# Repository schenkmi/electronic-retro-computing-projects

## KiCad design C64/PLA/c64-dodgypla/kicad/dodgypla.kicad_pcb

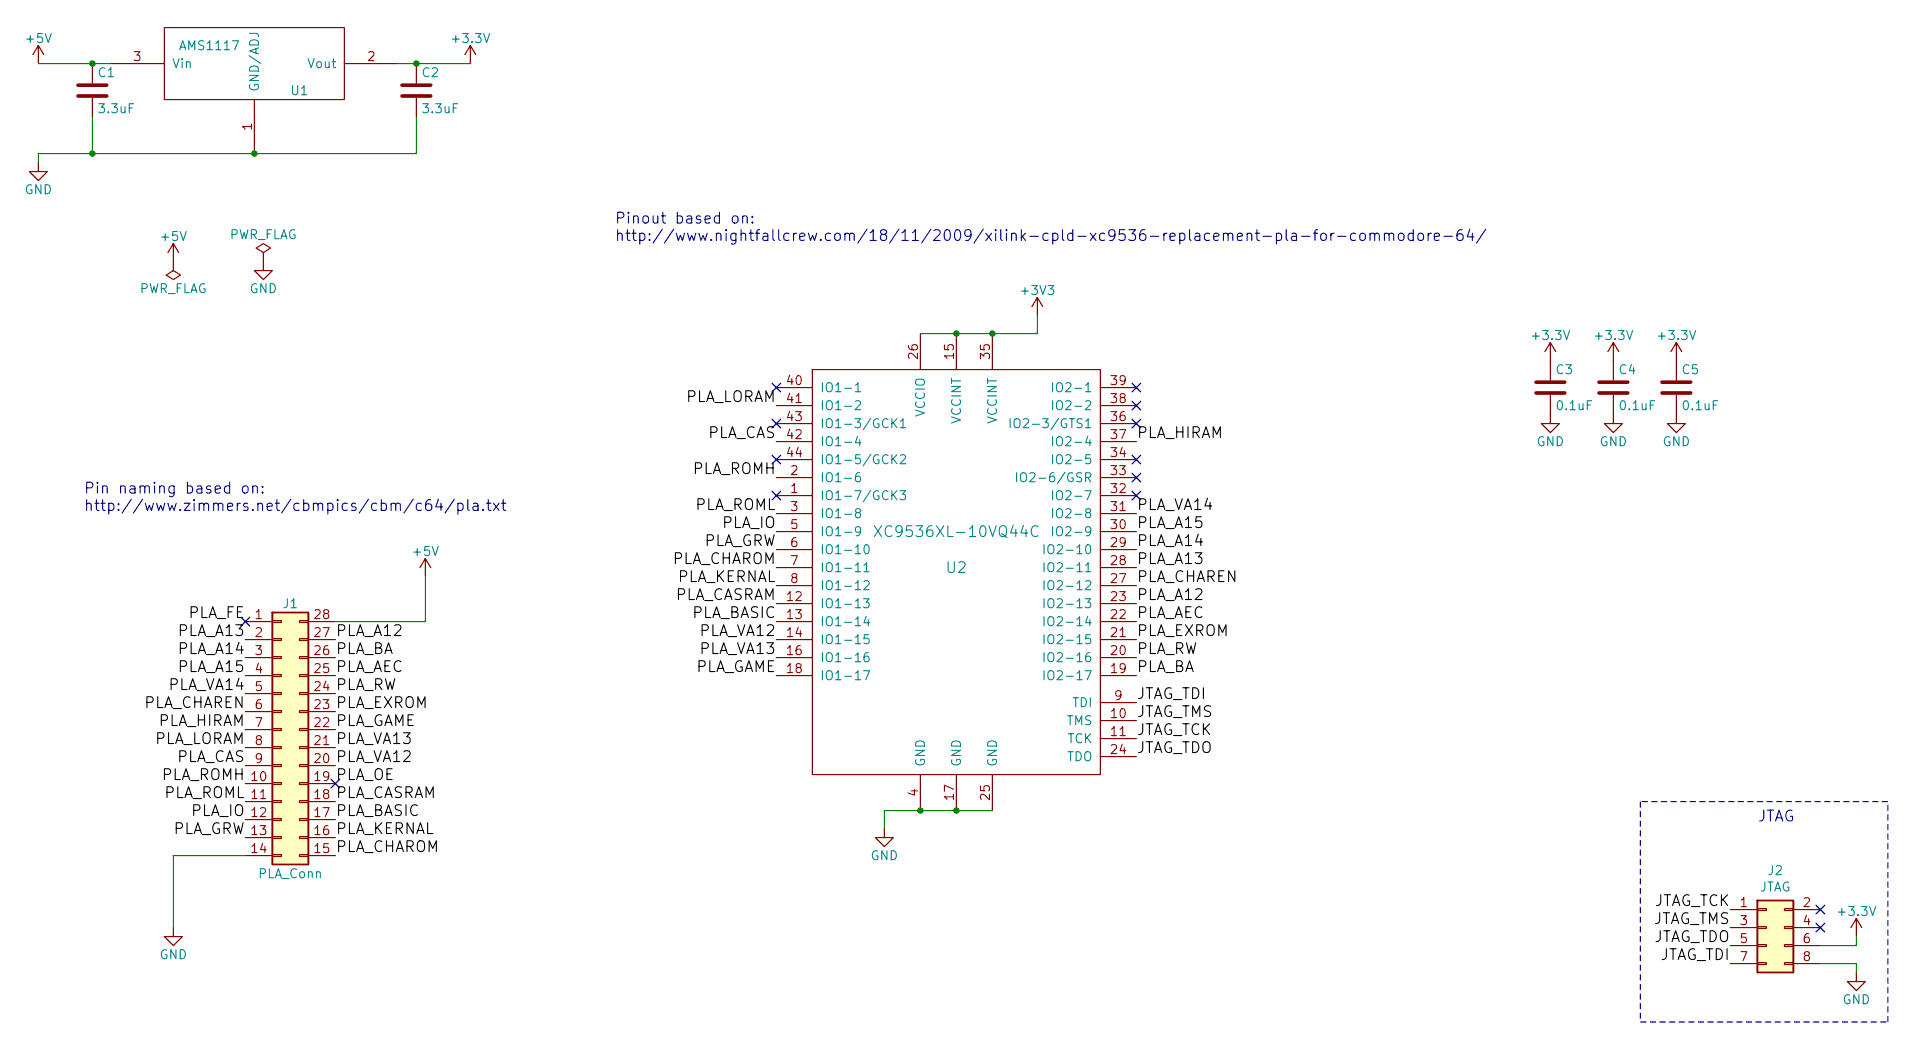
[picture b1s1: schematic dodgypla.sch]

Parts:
C1, C2: 3.3uF; C_0805
C3, C4, C5: 0.1uF; C_0805
J1: PLA_Conn; DIP-28_W15.24mm_Socket
J2: JTAG; Pin_Header_Straight_2x04_Pitch2.54mm
U1: AMS1117; SOT-223-3_TabPin2
U2: XC9536XL-10VQ44C; LQFP-44_10x10mm_P0.8mm

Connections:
+5V: C1.1, J1.28, U1.3 (Vin)
/JTAG_TCK: J2.1, U2.11 (TCK)
/JTAG_TDI: J2.7, U2.9 (TDI)
/JTAG_TDO: J2.5, U2.24 (TDO)
/JTAG_TMS: J2.3, U2.10 (TMS)
/PLA_A12: J1.27, U2.23 (IO2-13)
/PLA_A13: J1.2, U2.28 (IO2-11)
/PLA_A14: J1.3, U2.29 (IO2-10)
/PLA_A15: J1.4, U2.30 (IO2-9)
/PLA_AEC: J1.25, U2.22 (IO2-14)
/PLA_BA: J1.26, U2.19 (IO2-17)
/PLA_BASIC: J1.17, U2.13 (IO1-14)
/PLA_CAS: J1.9, U2.42 (IO1-4)
/PLA_CASRAM: J1.18, U2.12 (IO1-13)
/PLA_CHAREN: J1.6, U2.27 (IO2-12)
/PLA_CHAROM: J1.15, U2.7 (IO1-11)
/PLA_EXROM: J1.23, U2.21 (IO2-15)
/PLA_FE: J1.1
/PLA_GAME: J1.22, U2.18 (IO1-17)
/PLA_GRW: J1.13, U2.6 (IO1-10)
/PLA_HIRAM: J1.7, U2.37 (IO2-4)
/PLA_IO: J1.12, U2.5 (IO1-9)
/PLA_KERNAL: J1.16, U2.8 (IO1-12)
/PLA_LORAM: J1.8, U2.41 (IO1-2)
/PLA_OE: J1.19
/PLA_ROMH: J1.10, U2.2 (IO1-6)
/PLA_ROML: J1.11, U2.3 (IO1-8)
/PLA_RW: J1.24, U2.20 (IO2-16)
/PLA_VA12: J1.20, U2.14 (IO1-15)
/PLA_VA13: J1.21, U2.16 (IO1-16)
/PLA_VA14: J1.5, U2.31 (IO2-8)
GND: C1.2, C2.2, C3.2, C4.2, C5.2, J1.14, J2.8, U1.1 (GND/ADJ), U2.4 (GND), U2.17 (GND), U2.25 (GND)

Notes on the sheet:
Pin naming based on: http://www.zimmers.net/cbmpics/cbm/c64/pla.txt
Pinout based on: http://www.nightfallcrew.com/18/11/2009/xilink-cpld-xc9536-replacement-pla-for-commodore-64/
JTAG

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
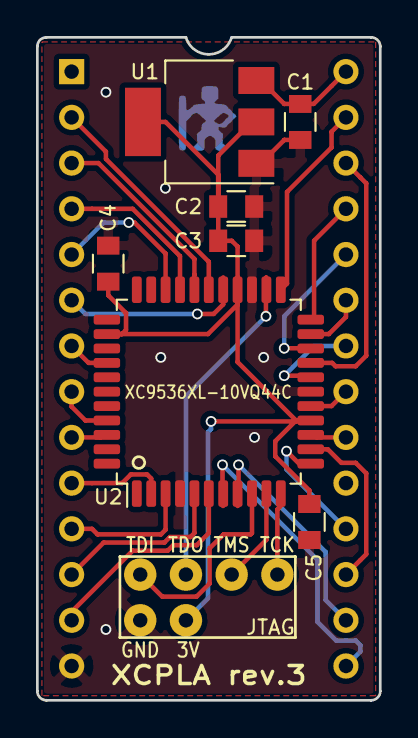
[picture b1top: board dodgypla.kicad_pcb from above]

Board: 2 copper layers, 19.0 x 36.8 mm, 9 parts (0 on the bottom side), 31 nets.

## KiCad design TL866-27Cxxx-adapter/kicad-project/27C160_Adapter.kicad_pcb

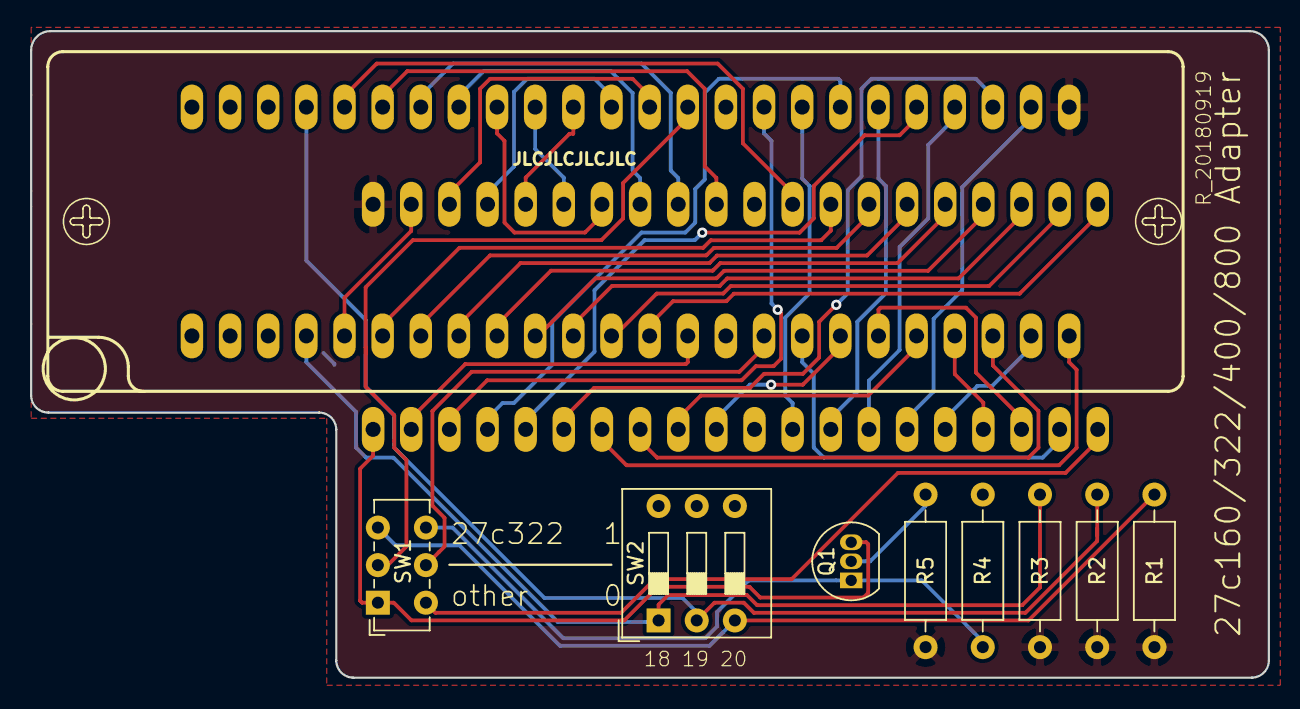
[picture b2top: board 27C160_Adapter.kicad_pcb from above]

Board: 2 copper layers, 82.4 x 43.1 mm, 11 parts (0 on the bottom side), 46 nets.

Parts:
Q1: BC327; TO-92_Inline
R1, R2, R3, R4, R5: 10k; R_Axial_DIN0207_L6.3mm_D2.5mm_P10.16mm_Horizontal
REF01: OSHW-Logo2_9.8x8mm_SilkScreen
SW1: MS22D16; SW_E-Switch_EG1271_DPDT
SW2: SW_DIP_x03; SW_DIP_SPSTx03_Slide_9.78x9.8mm_W7.62mm_P2.54mm
U1: 27C4002
ZX1: 3M_248-3345

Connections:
/A0: U1.21, ZX1.13
/A1: U1.22, ZX1.12
/A2: U1.23, ZX1.11
/A3: U1.24, ZX1.10
/A4: U1.25, ZX1.9
/A5: U1.26, ZX1.8
/A6: U1.27, ZX1.7
/A7: U1.28, ZX1.6
/A8: U1.29, ZX1.44
/A9: U1.31, ZX1.43
/A10: U1.32, ZX1.42
/A11: U1.33, ZX1.41
/A12: U1.34, ZX1.40
/A13: U1.35, ZX1.39
/A14: U1.36, ZX1.38
/A15: U1.37, ZX1.37
/A16: U1.38, ZX1.36
/A17: U1.39, ZX1.5
/A18: R3.1, SW2.1, ZX1.4
/A19: R2.1, SW2.2, ZX1.45
/A20: R1.1, SW1.3, SW2.3
/D0: U1.19, ZX1.17
/D1: U1.18, ZX1.19
/D2: U1.17, ZX1.21
/D3: U1.16, ZX1.23
/D4: U1.15, ZX1.26
/D5: U1.14, ZX1.28
/D6: U1.13, ZX1.30
/D7: U1.12, ZX1.32
/D8: U1.10, ZX1.18
/D9: U1.9, ZX1.20
/D10: U1.8, ZX1.22
/D11: U1.7, ZX1.24
/D12: U1.6, ZX1.27
/D13: U1.5, ZX1.29
/D14: U1.4, ZX1.31
/D15: U1.3, ZX1.33
/E: U1.2, ZX1.14
/N$1: Q1.2, R5.2
/N$2: SW1.2, ZX1.35
/N$4: Q1.1, R4.1, SW1.6
/N$5: SW1.4, U1.20
/N$6: SW1.5, ZX1.16
/VPP: Q1.3, SW1.1, U1.1
GND: R4.2, SW2.4, SW2.5, SW2.6, U1.11, U1.30, ZX1.15, ZX1.34
VCC: R1.2, R2.2, R3.2, R5.1, U1.40, ZX1.25

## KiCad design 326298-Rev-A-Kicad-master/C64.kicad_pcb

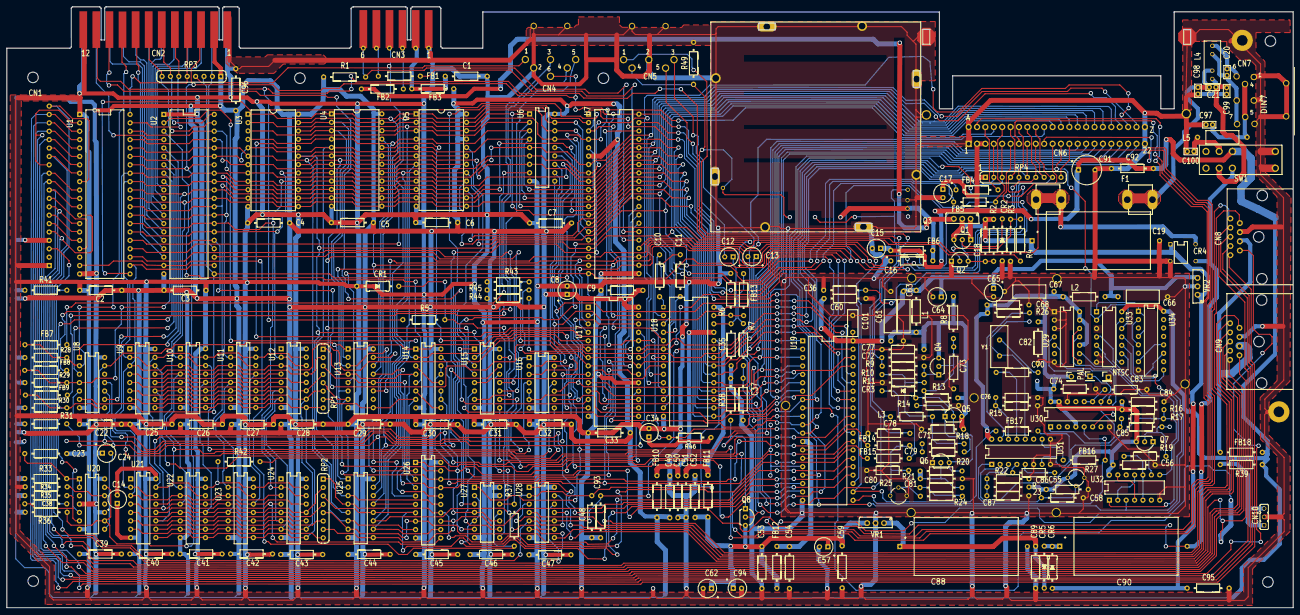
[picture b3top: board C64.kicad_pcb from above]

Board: 2 copper layers, 389.2 x 181.8 mm, 237 parts (0 on the bottom side), 234 nets.

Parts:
C1, C2, C3, C16, C18, C22, C30, C31, C32, C35, C39, C45, C46, C47, C55, C56, C58, C68, C71, C74, C76, C77, C82, C84, C87, C89, C95, C96: 0.1 uF; 12_03_07
C4, C5, C6, C7, C9, C29, C33, C44, C51, C60, C85: 0.47 uF; 12_03_07
C8, C12, C13, C14, C15, C17, C24, C34, C57, C62, C64, C65, C94: 10 uF 25V; CAPACITOR_ELECTROLYTIC_2.5_6
C10, C11: 2200 pF Polyester; polyester12_03_07
C19: 2200 uF 16V; E37-31.5-17.5-E
C20, C21, C97, C98, C99, C100: 0.22 uF 100V; 0203
C23: 360 pF; 12_03_07
C25, C26, C27, C28, C40, C41, C42, C43, C50, C53, C59, C92: 0.22 uF; 12_03_07
C36: 20 pF 50V; 12_03_07
C37, C48, C93: 1000 pF; 12_03_07
C38, C80: 51 pF; 12_03_07
C49, C52: 470 pF 50V; 12_03_07
C54: 470 pF; 12_03_07
C61, C63, C66, C67: 0.47 uF 50V 20%; 15_4_10
C70: 10 pF 5%; 12_03_07
C72, C78: 220 pF 50V; 12_03_07
C73: 150 pF 50V; 12_03_07
C79: 510 pF; 12_03_07
C81: 20 pF; 12_03_07
C83: 33 pF; 12_03_07
C86: 39 pF 50V 5%; 12_03_07
C88, C90: 470 uF 50V; E37-31.5-17.5-E
C91: 100 uF 16V; C_E_5-9
C101: 0.1 uF; c101
CN1: KEYBOARD; 20way
CN2: USERPORT
CN3: CASSETTEPORT
CN4: DIN6
CN5: DIN5
CN6: EXPANSIONPORT
CN7: DIN7
CN8, CN9: CONTROL_PORT
CN10: JP2E; 3way
CR1: 1N4371 2.7 V; D-12_3_7
CR2: 7.5 V; D-12_3_7
CR3: 1N914; D-12_3_7
CR4: BRIDGE_RECTIFIER
CR5, CR6: 1N4001; D-12_3_7
F1: 1A; SH32
FB1, FB2, FB3, FB4, FB5, FB6, FB7, FB8, FB9, FB10, FB11, FB12, FB13, FB14, FB15, FB16, FB17, FB18: FERRITE_BEAD
J1, J2, J3: Conn_01x01; Socket_Strip_Straight_1x01_Pitch2.54mm
L1, L2: 2.2 uH; 12_03_07
L3: 3 uH; 12_03_07
L4: LINEFILTER
L5: 1.2 uH; P15
Q1: 2N4401; TO92
Q2: 2N3904; TO92
Q3: TIP29B
Q4, Q5, Q6, Q7, Q8: PN2222; TO92
R1, R24, R43, R44, R45: 3.3 K; 12_03_07
R2, R5, R15, R22: 1.5 K; 12_03_07
R3, R7: 10 K; 12_03_07
R4, R6, R13, R16, R23, R28, R29, R30, R31, R36, R38: 1 K; 12_03_07
R8, R39: 390; 12_03_07
R9, R26: 75; 12_03_07
R10, R11: 120; 12_03_07
R14: 100; 12_03_07
R17: 1.2 K; 12_03_07
R18: 230; 12_03_07
R19: 15 K; 12_03_07
R20, R37: 6.8 K; 12_03_07
R21: 4.7 K; 12_03_07
R25: 1 K Trim Pot; POT_METER
R27: 2 K Trim Pot; POT_METER
R33, R34: 47 K; 12_03_07
R35: 470 K; 12_03_07
R41: 1 M; 12_03_07
R42: 0; 12_03_07
R46: 2.1 K; 12_03_07
R49: 470; 12_03_07
RF1: RF-MODULATOR
RP1, RP2: 33; RESISTOR_PACK_4
RP3: 3.3 K; RESISTOR_PACK_4
RP4: 3.3 K; RESISTOR_PACK_9
SW1: DPDT_SWITCH
U1, U2: 6526
U3, U4: 2364
U5: 2332
U6: 2114
U7: 6510
U8: SN7406NN
U9, U10, U11, U12, U21, U22, U23, U24: 4164
U13, U25: SN74257N
U14: SN74258N
U15: SN74139N
U16, U28: 4066
U17: C64PLA
U18: 6581
U19: 6569
U20: 556DIGITAL
U26: SN74373N; 74373N
U27: SN7408N
U29: SN7474N
U30: SN74193N
U31: SN74629
U32: MC4044
U33: 74LS02; 7402
U34: 74LS175; SN74629
VR1: 7812; VR
VR2: 7805; VR
Y1: 17.73 MHz; HC49TL-H

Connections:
/+5Vc: C55.1, C56.1, C67.1, C68.1, C74.1, C82.1, C84.1, J1.1, L2.2, Q7.3, R16.1, R23.1, R26.1, R27.E, U29.10, U29.13, U29.14, U30.4, U30.15, U30.16, U31.16, U32.14
/+5Vcan: C60.1, C63.1, C64.+, C65.+, C66.1, C101.1, L1.1, L2.1, U19.40, VR2.3
/+5Vvid: C61.1, C71.1, C77.1, L1.2, Q4.3, Q5.3, R8.1, R13.1
/+9V: C18.1, C19.+, C95.1, CR4.1, CR6.1, Q1.3, Q3.2, R2.1, VR2.1
/+12V: C52.1, C53.1, C57.+, C59.1, C62.+, C94.+, FB11.1, FB12.1, Q8.3, VR1.3
/A0: CN6.Y, U1.38, U2.38, U3.8, U4.8, U5.8, U6.5, U7.7, U18.9, U25.13, U26.6
/A1: CN6.X, U1.37, U2.37, U3.7, U4.7, U5.7, U6.6, U7.8, U18.10, U25.10, U26.12
/A2: CN6.W, U1.36, U2.36, U3.6, U4.6, U5.6, U6.7, U7.9, U18.11, U25.6, U26.9
/A3: CN6.V, U1.35, U2.35, U3.5, U4.5, U5.5, U6.4, U7.10, U18.12, U25.3, U26.15
/A4: CN6.U, U3.4, U4.4, U5.4, U6.3, U7.11, U13.13, U18.13, U26.16
/A5: CN6.T, U3.3, U4.3, U5.3, U6.2, U7.12, U13.6, U26.19
/A6: CN6.S, U3.2, U4.2, U5.2, U6.1, U7.13, U13.3, U26.5
/A7: CN6.R, U3.1, U4.1, U5.1, U6.17, U7.14, U26.2
/A8: CN6.P, U3.23, U4.23, U5.23, U6.16, U7.15, U15.14, U19.32, U25.14
/A9: CN6.N, U3.22, U4.22, U5.22, U6.15, U7.16, U15.13, U19.33, U25.11
/A10: CN6.M, U3.19, U4.19, U5.19, U7.17, U15.2, U19.34, U25.5
/A11: CN6.L, U3.18, U4.18, U5.18, U7.18, U15.3, U19.23, U25.2
/A12: CN6.K, RP4.9, U3.21, U4.21, U7.19, U13.14, U17.27
/A13: CN6.J, RP4.7, U7.20, U13.5, U17.2
/A14: CN6.H, RP4.5, U7.22, U13.2, U17.3
/A15: CN6.F, RP4.4, U7.23, U13.11, U17.4
/D0: CN6.21, U1.33, U2.33, U3.9, U4.9, U5.9, U7.37, U16.11, U18.15, U19.7, U21.2, U21.14
/D1: CN6.20, U1.32, U2.32, U3.10, U4.10, U5.10, U7.36, U9.2, U9.14, U16.8, U18.16, U19.6
/D2: CN6.19, U1.31, U2.31, U3.11, U4.11, U5.11, U7.35, U16.4, U18.17, U19.5, U22.2, U22.14
/D3: CN6.18, U1.30, U2.30, U3.13, U4.13, U5.13, U7.34, U10.2, U10.14, U16.1, U18.18, U19.4
/D4: CN6.17, U1.29, U2.29, U3.14, U4.14, U5.14, U7.33, U18.19, U19.3, U23.2, U23.14
/D5: CN6.16, U1.28, U2.28, U3.15, U4.15, U5.15, U7.32, U11.2, U11.14, U18.20, U19.2
/D6: CN6.15, U1.27, U2.27, U3.16, U4.16, U5.16, U7.31, U18.21, U19.1, U24.2, U24.14
/D7: CN6.14, U1.26, U2.26, U3.17, U4.17, U5.17, U7.30, U12.2, U12.14, U18.22, U19.39
/GND: C1.2, C2.2, C3.2, C4.2, C5.2, C6.2, C7.2, C8.-, C9.2, C14.-, C15.-, C16.2, C17.-, C19.-, C22.2, C23.2, C25.2, C26.2, C27.2, C28.2, C29.2, C30.2, C31.2, C32.2, C33.2, C34.-, C35.2, C36.2, C37.2, C39.2, C40.2, C41.2, C42.2, C43.2, C44.2, C45.2, C46.2, C47.2, C48.1, C49.2, C50.2, C51.2, C52.2, C53.2, C54.2, C55.2, C56.2, C57.-, C58.2, C59.2, C60.2, C61.2, C62.-, C63.2, C64.-, C65.-, C66.2, C67.2, C68.2, C71.2, C72.2, C73.2, C74.2, C76.2, C77.2, C78.2, C80.2, C82.2, C83.2, C84.2, C87.2, C88.-, C89.2, C91.-, C92.2, C93.1, C94.-, C95.2, C96.2, C97.2, C98.2, C99.2, C100.2, C101.2, CN1.1, CN2.1, CN2.12, CN2.A, CN2.N, CN3.1, CN3.A, CN4.2, CN4.PE, CN4.PE@, CN5.2, CN5.PE, CN5.PE@, CN6.1, CN6.22, CN6.A, CN6.P$1, CN6.P$2, CN6.P$3, CN6.P$4, CN6.Z, CN7.1, CN7.2, CN7.3, CN7.PE, CN7.PE@, CN8.8, CN9.8, CN10.2, CR1.1, CR2.1, CR4.2, J2.1, Q2.1, Q6.1, R3.2, R6.2, R11.1, R14.2, R15.2, R21.2, R22.2, R25.E, R27.A, R34.1, R38.2, R49.2, RF1.CASE, RF1.P$1, RF1.P$2, RF1.P$3, RF1.P$4, RF1.P$5, RF1.P$6, RF1.P$7, RF1.P$8, SW1.7, SW1.8, U1.1, U2.1, U3.12, U4.12, U5.12, U6.9, U7.21, U8.7, U9.16, U10.16, U11.16, U12.16, U13.8, U14.8, U15.8, U16.7, U17.14, U17.19, U18.14, U19.20, U20.7, U21.16, U22.16, U23.16, U24.16, U25.8, U26.10, U27.7, U28.7, U29.1, U29.2, U29.3, U29.7, U30.8, U30.14, U31.6, U31.8, U31.9, U32.7, U33.3, U33.6, U33.7, U34.8, VR1.2, VR2.2
/IRQ: CN6.4, RP4.2, U1.21, U7.3, U19.8
/MA0: RP2.4, U9.5, U10.5, U11.5, U12.5, U21.5, U22.5, U23.5, U24.5
/MA1: RP2.8, U9.7, U10.7, U11.7, U12.7, U21.7, U22.7, U23.7, U24.7
/MA2: RP2.6, U9.6, U10.6, U11.6, U12.6, U21.6, U22.6, U23.6, U24.6
/MA3: RP2.2, U9.12, U10.12, U11.12, U12.12, U21.12, U22.12, U23.12, U24.12
/MA4: RP1.4, U9.11, U10.11, U11.11, U12.11, U21.11, U22.11, U23.11, U24.11
/MA5: RP1.6, U9.10, U10.10, U11.10, U12.10, U21.10, U22.10, U23.10, U24.10
/MA6: RP1.2, U9.13, U10.13, U11.13, U12.13, U21.13, U22.13, U23.13, U24.13
/MA7: RP1.8, U9.9, U10.9, U11.9, U12.9, U21.9, U22.9, U23.9, U24.9
/N$1: C12.+, C35.1, U18.26
/N$2: FB13.1, R6.1, U18.27
/N$3: FB13.2, R7.1
/N$4: C37.1, Q8.2, R7.2
/N$5: C13.+, Q8.1, R38.1
/N$6: C10.2, U18.2
/N$7: C11.2, U18.4
/N$8: C10.1, U18.1
/N$9: C11.1, U18.3
/N$10: C13.-, CN5.3, RF1.AUDI
/N$11: C12.-, CN5.5
/N$12: C34.+, C50.1, FB10.1, R46.1, U18.25
/N$13: C16.1, FB6.2, RF1.+
/N$14: C51.1, FB11.2, U18.28
/N$15: C80.1, FB14.2, R25.A
/N$16: FB14.1, U19.14
/N$17: C97.1, CN7.4, CN7.5, L5.1
/N$18: C100.1, L5.2, SW1.2
/N$19: C20.2, CN7.6, L4.4
/N$20: C20.1, CN7.7, L4.2
/N$21: C21.1, C98.1, F1.1A, F1.1B, L4.3
/N$22: C21.2, C99.1, L4.1, SW1.5
/N$23: CN2.11, CR4.4, F1.2A, F1.2B, R5.1
/N$24: C90.-, CN2.10, CR4.3, SW1.6
/N$26: C90.+, CR5.1, CR6.2
/N$27: C88.+, C89.1, CR5.2, VR1.1
/N$28: R24.1, R25.S
/N$29: C81.2, R24.2
/N$30: C81.1, Q6.2, R20.1, R21.1
/N$31: Q5.2, Q6.3, R13.2, R20.2
/N$32: C79.2, Q5.1, R14.1
/N$33: L3.1, R10.2, R11.2, R18.1
/N$35: C54.1, FB12.2, U19.13
/N$36: C73.1, CR3.1, Q4.2, R8.2
/N$37: CR3.2, FB15.2
/N$38: Q4.1, R9.1, R10.1
/N$39: C72.1, CN5.1, R9.2
/N$41: C78.1, CN5.4, L3.2, R49.1, RF1.VIDE
/N$42: U14.10, U14.11, U19.31
/N$44: U14.13, U14.14, U19.30
/N$45: U14.3, U14.12
/N$46: U14.6, U14.9
/N$47: U6.14, U16.10, U19.38
/N$48: U6.13, U16.9, U19.37
/N$49: U6.12, U16.3, U19.36
/N$50: U6.11, U16.2, U19.35
/N$51: R42.2, U17.18
/N$52: U8.11, U14.15, U16.5, U16.6, U16.12, U16.13, U19.16, U26.1, U27.4, U27.10
/N$53: U8.13, U13.1, U14.1, U17.9, U19.19, U25.1
/N$54: R42.1, U9.15, U10.15, U11.15, U12.15, U21.15, U22.15, U23.15, U24.15
/N$55: U9.4, U10.4, U11.4, U12.4, U19.18, U21.4, U22.4, U23.4, U24.4, U26.11
/N$56: U6.8, U27.8
/N$59: C24.-, R34.2, U20.8, U20.12
/N$60: U8.5, U20.5
/N$61: C23.1, R33.2, U20.1, U20.2
/N$62: C38.2, R35.1, U20.6
/N$63: C38.1, CN1.3, R41.2
/N$64: R26.2, U31.15
/N$65: C58.1, R27.S, U31.1
/N$66: FB16.1, U31.10
/N$67: C70.2, U31.13
/N$68: U31.12, Y1.2
/N$69: C70.1, Y1.1
/N$70: FB16.2, U19.21, U30.5
/N$71: C83.1, U30.11, U30.12
/N$72: J3.1, U29.4, U30.1, U30.10
/N$73: U29.5, U30.9
/N$74: R16.2, R17.2, U31.2, U32.8
/N$75: U29.11, U30.6
/N$76: U29.8, U29.12
/N$77: U32.2, U32.11
/N$78: U32.4, U32.13
/N$79: C87.1, R22.1, R23.2, U31.3
/N$80: C86.1, U31.4
/N$81: C86.2, U31.5
/N$82: FB17.1, U31.7
/N$83: U29.9, U32.1
/N$84: CN3.5, CN3.E, FB1.1
/N$85: R19.2, U32.5, U32.10
/N$86: C85.1, R17.1
/N$87: C36.1, CN6.6, FB17.2, U19.22
/N$88: C85.2, Q7.2, R19.1
/N$89: R31.2, U8.10, U13.15, U17.25, U25.15
/N$90: Q7.1, U32.9
/N$91: CN1.19, CN8.2, U1.3
/N$92: CN1.18, CN8.3, U1.4
/N$93: CN1.17, CN8.4, U1.5
/N$94: CN1.16, CN8.6, U1.6
/N$95: CN1.15, U1.7
/N$96: CN1.14, U1.8, U28.6, U28.12
/N$97: CN1.20, U1.9, U28.5, U28.13
/N$98: CN1.13, CN8.1, U1.2
/N$99: CN1.12, CN9.1, U1.10
/N$100: CN1.11, CN9.2, U1.11
/N$101: CN1.10, CN9.3, U1.12
/N$102: CN1.9, U1.17
/N$103: CN1.8, CN9.6, U1.14, U19.9
/N$104: CN1.7, U1.15
/N$105: CN1.5, CN9.4, U1.13
/N$106: CN1.6, U1.16
/N$107: CN8.9, U28.1
/N$108: CN8.5, U28.4
/N$109: CN8.7, CN9.7, FB18.1
/N$110: CN9.9, U28.8
/N$111: CN9.5, U28.11
/N$112: C48.2, U18.24, U28.2, U28.9
/N$113: C93.2, U18.23, U28.3, U28.10
/N$114: CN4.3, FB7.1
/N$115: CN4.4, FB9.1
/N$116: CN4.5, FB8.1
/N$117: FB8.2, R29.2, U2.9, U8.4
/N$118: FB9.2, R30.2, U2.8, U8.8
/N$119: CN2.9, FB7.2, R28.2, U8.2
/N$120: CN2.8, U2.18
/N$121: CN2.L, U2.17
/N$122: CN2.K, U2.16
/N$123: CN2.J, U2.15
/N$124: CN2.H, U2.14
/N$125: CN2.F, U2.13
/N$126: CN2.E, U2.12
/N$127: CN2.D, U2.11
/N$128: CN2.C, U2.10
/N$129: CN2.B, RP3.2, U2.24
/N$130: U2.7, U8.3
/N$131: U2.6, U8.9
/N$132: U2.5, U8.1
/N$133: CN3.3, CN3.C, FB2.1
/N$134: CN2.4, RP3.5, U1.40
/N$135: U2.2, U14.2, U17.5
/N$136: U2.3, U14.5
/N$137: CN2.M, U2.4
/N$138: CN2.7, RP3.8, U2.39
/N$139: CN2.6, RP3.7, U2.40
/N$140: CN2.5, RP3.6, U1.39
/N$141: FB5.1, U7.39
/N$143: C76.1, R15.1, U31.14
/N$145: U3.20, U17.17
/N$146: CR1.2, R5.2, R37.2, U27.12
/N$147: R37.1, U1.19, U2.19, U27.11
/N$148: CN10.1, CN10.3, R39.2
/N$152: U4.20, U17.16
/N$153: CN6.C, FB4.1
/N$155: CN6.12, U17.26, U19.12, U27.1, U33.2, U33.12
/N$157: CN6.11, U17.11
/N$158: CN6.B, U17.10
/N$159: CN6.9, RP4.8, U17.23
/N$160: CN6.8, RP4.6, U17.22
/N$162: FB15.1, U19.15
/N$163: U15.4, U19.10
/N$164: R45.2, U7.29, U17.8
/N$165: R44.2, U7.28, U17.7
/N$166: R43.2, U7.27, U17.6
/N$167: U7.2, U27.3
/N$168: U7.5, U27.6
/N$169: CN6.13, RP4.10, U27.2, U27.5
/N$170: U5.20, U17.15
/N$171: CN3.4, CN3.D, CN4.1, RP3.4, U1.24
/N$172: CN3.6, CN3.F, R1.2, U7.25
/N$173: C1.1, CN3.2, CN3.B, FB3.1
/N$176: FB1.2, U7.26
/N$177: Q2.2, R3.1, R4.2
/N$178: Q1.1, Q3.1
/N$179: C18.2, CR2.2, Q1.2, Q2.3, R2.2
/N$180: FB2.2, Q3.3
/N$181: R4.1, U7.24
/N$182: U1.23, U15.12
/N$183: U2.23, U15.11
/N$184: U6.10, U17.13
/N$185: U15.1, U17.12
/N$186: U15.7, U15.15
/N$187: CN6.7, U15.10
/N$188: CN6.10, U15.9
/N$189: U15.5, U18.8
/N$190: U15.6, U27.9
/NA0: RP2.3, U19.24, U25.12, U26.7
/NA1: RP2.7, U19.25, U25.9, U26.13
/NA2: RP2.5, U19.26, U25.7, U26.8
/NA3: RP2.1, U19.27, U25.4, U26.14
/NA4: RP1.3, U13.12, U17.20, U19.28, U26.17
/NA5: RP1.5, U13.7, U17.21, U19.29, U26.18
/NA6: RP1.1, U13.4, U14.4, U26.4
/NA7: RP1.7, U13.9, U14.7, U26.3
/NMI: CN6.D, RP3.3, U2.21, U7.4, U8.6
/PHI0: U7.1, U19.17, U32.3, U33.5
/PHI2: CN6.E, FB5.2, U1.25, U2.25, U18.6
/RES: CN2.3, CN4.6, FB4.2, R36.2, U1.34, U2.34, U7.40, U18.5, U20.9, U20.13
/RW: CN6.5, R46.2, RP4.3, U1.22, U2.22, U7.38, U9.3, U10.3, U11.3, U12.3, U17.24, U18.7, U19.11, U21.3, U22.3, U23.3, U24.3
/VCC: C2.1, C3.1, C4.1, C5.1, C6.1, C7.1, C8.+, C9.1, C14.+, C15.+, C17.+, C22.1, C24.+, C25.1, C26.1, C27.1, C28.1, C29.1, C30.1, C31.1, C32.1, C33.1, C39.1, C40.1, C41.1, C42.1, C43.1, C44.1, C45.1, C46.1, C47.1, C49.1, C91.+, C92.1, C96.1, CN1.4, CN2.2, CN6.2, CN6.3, FB3.2, FB6.1, FB10.2, FB18.2, R1.1, R28.1, R29.1, R30.1, R31.1, R33.1, R35.2, R36.1, R39.1, R41.1, R43.1, R44.1, R45.1, RP3.1, RP4.1, SW1.3, U1.20, U2.20, U3.24, U4.24, U5.21, U5.24, U6.18, U7.6, U8.14, U9.8, U10.8, U11.8, U12.8, U13.16, U14.16, U15.16, U16.14, U17.28, U20.4, U20.10, U20.14, U21.8, U22.8, U23.8, U24.8, U25.16, U26.20, U27.13, U27.14, U28.14, U33.14, U34.16
unnamed: C79.1, R18.2
unnamed: U33.1, U34.1, U34.4
unnamed: U33.4, U33.9, U34.9
unnamed: U33.11, U34.11
unnamed: U33.8, U33.13
unnamed: U34.2, U34.5
unnamed: U34.7, U34.12

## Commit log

2023-07-29 Adding misc retro computing projects from the inetnert
2024-07-10 DIMM Modul
2024-07-10 Adding KiCad Retro
2024-07-17 Add EPROM EMU NG from
    https://github.com/Kris-Sekula/EPROM-EMU-NG
    https://mygeekyhobby.com/2020/07/05/eprom-emulator/
2024-07-20 https://github.com/MicroCoreLabs
    https://github.com/MicroCoreLabs/Projects
    Ted Fried's MicroCore Labs Projects which include microsequencer-based FPGA cores and emulators for the 8088, 8086, 8051, 6502, 68000, Z80, Risc-V, and also Typewriter and EPROM Emulator projects. MC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
2024-11-06 Add PicoROM from https://github.com/wickerwaka/PicoROM
    Add PicoROM from https://github.com/wickerwaka/PicoROM
2024-11-24 BlueSCSI-v2
    https://github.com/BlueSCSI/BlueSCSI-v2
2024-12-27 Various retro things from github
2025-01-15 Added from https://github.com/silvervest
    SIMM for STM
    TL866-27Cxxx Adapter
    From https://github.com/silvervest
2025-01-22 Adding projects from https://github.com/slu4coder
    https://github.com/slu4coder
2025-01-22 https://github.com/mist64
    From https://github.com/mist64
2025-01-22 https://github.com/eduardocasino
    From https://github.com/eduardocasino
2025-01-22 https://github.com/tebl
    From https://github.com/tebl
2025-01-23 https://github.com/frntc
    Added from https://github.com/frntc
2025-02-15 Adding Dodgy PLA
    https://github.com/hackup/c64-dodgypla
2025-02-16 More PLAs
2025-04-09 Adding some Atari ST projects
    https://github.com/tomtebloss/ATARI-RAM-upgrades
    https://github.com/retro16/acsi2stm
